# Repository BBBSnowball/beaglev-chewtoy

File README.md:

This is a fairly simple little board targetted at the BeagleV, but likely usable for anything that uses a 2x20 pin header.

The board takes the existing 2x20 header and either via a through-hole, or smt, header extends it away from the board
(assuming the connector is on the edge), and rotates it 180deg so if you happen to have a large heat sink, or something
else that's blocking the pins they might still be accessible for hats, etc. Most pre-production beta BeagleV boards have a
large heatsink out of an abundance of caution but this is not required and won't be used for production units.

This fork adds:
- LEDs: They are behind a buffer so the SoC or external device doesn't have to drive their current.
- series resistors: They provide some protection if you accidentally connect two outputs or while the SoC is driving
  the pins during reset. Remove them or use lower values if they impact high speed signals.
- JTAG headers: ARM 10-pin (2.54 mm and 1.27 mm, via ribbon cable), Sipeed RV Debugger (directly plugged into the board)
- a second header for debugging (e.g. attach a hat and a logic analyzer at the same time)
- UART connector
- pullups for I2C

All additional features are optional. Don't place the things that you don't need and you can close the solder jumper
below the series resistors if you don't want those. However, if you don't need any of them, I suggest that you use warthog9's
board: It's half the size and doesn't extend to the sides. Mine sacrifices that for a bit more functionality.

Jumpers:
- enable LEDs
- enable RX/TX on the Sipeed connector
  - You have to disable that if you want to use a different UART adapter, e.g. if you
    have trouble assigning different drivers to the parts of the FT2232H on Windows.
  - If you are on Linux, close the solder jumpers and omit the jumpers.
- connect 3.3V and/or 5V to Sipeed connector (solder jumpers)
  - The adapter doesn't need any reference voltage and it doesn't provide enough current to power the board so you should keep them open.
- swap TDI/TDO on the ARM connectors (solder jumpers)
  - I haven't tested the pinout yet so just in case...
- disconnect GND from pin 9 of the ARM connectors (GNDDetect)
- disconnect 3.3V from pin 1 of the ARM connectors
  - JTAG adapters with level shifters will use this to detect the target voltage.
  - If your adapter tries to power the target via this pin, cut the jumper to avoid that.

# Where to get one built

* OSH Park https://oshpark.com/shared_projects/uNRCdQbW (TODO: update this for the fork)

# License and Copyright
(C) John 'Warthog9' Hawley 2021, snowball 2021
CC-BY-SA 4.0

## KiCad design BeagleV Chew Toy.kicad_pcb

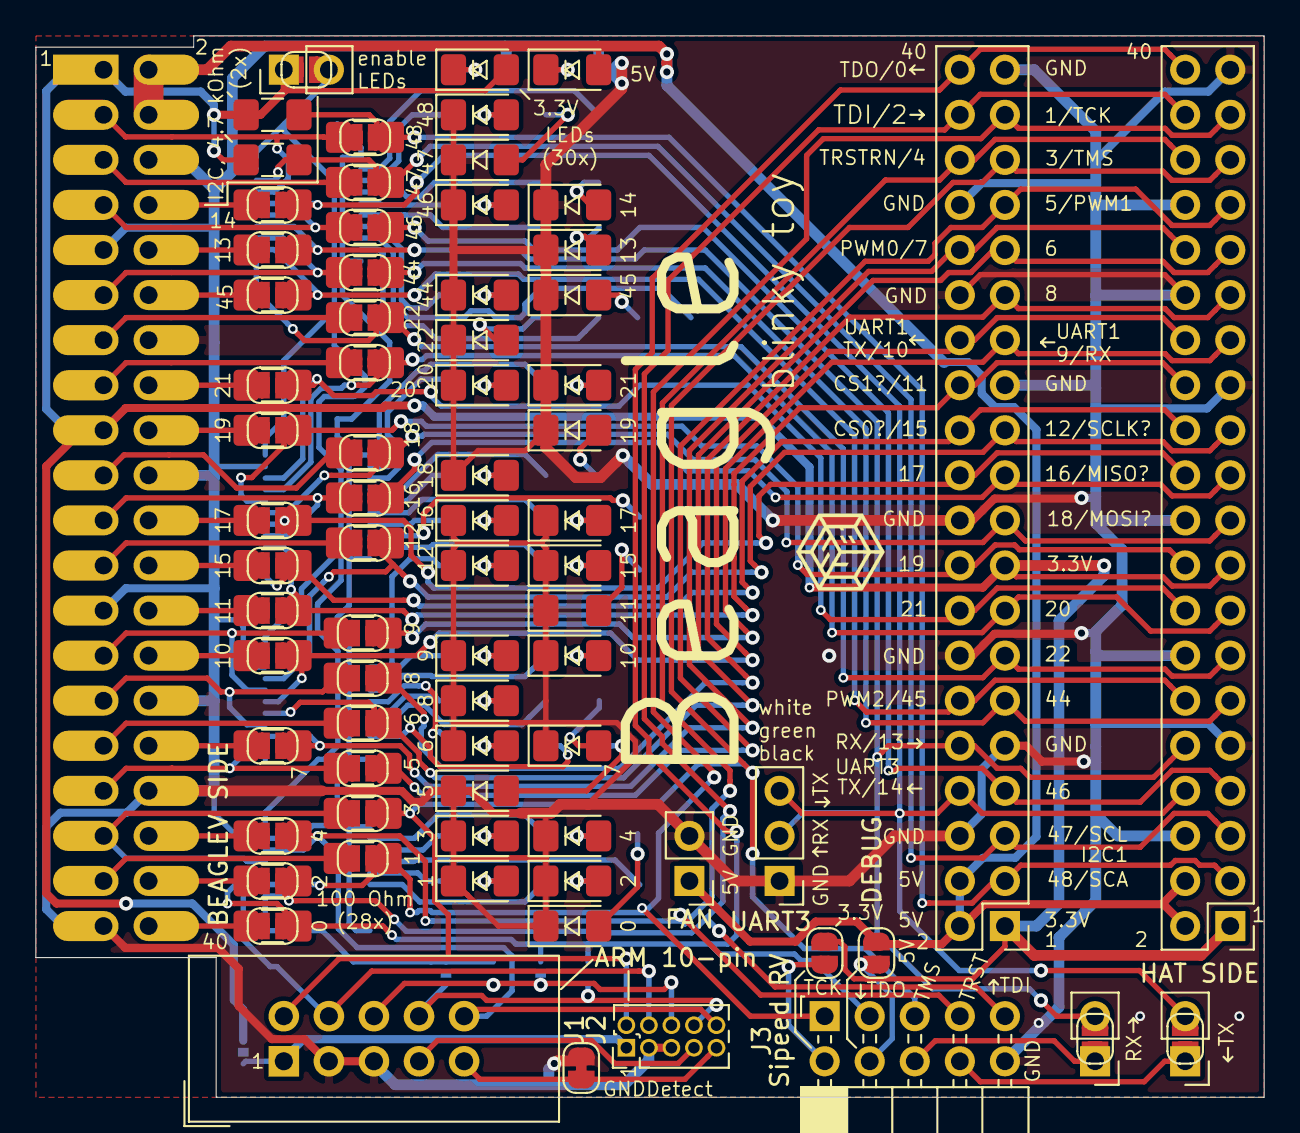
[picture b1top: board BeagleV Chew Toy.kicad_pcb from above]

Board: 2 copper layers, 69.2 x 59.8 mm, 148 parts (0 on the bottom side), 127 nets.

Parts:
BEAGLEVSIDE1: PINHD-2X20; PinSocket_2x20_P2.54mm_Vertical_THTSMD
C1, C2, C3, C4: 100nF; C_1206_3216Metric_Pad1.42x1.75mm_HandSolder
D1, D2, D3, D5, D7, D8, D10, D11, D12, D13, D15, D16, D18, D19, D21, D22, D23, D24, D26, D27, D28, D29, D31, D32, D33, D35, D36, D37, D38, D40: LED; LED_1206_3216Metric_Pad1.42x1.75mm_HandSolder
DEBUG1: PINHD-2X20-BIG; PinHeader_2x20_P2.54mm_Vertical
FAN1: PINHD-1X2; PinHeader_1x02_P2.54mm_Vertical
HATSIDE1: PINHD-2X20-BIG; PinHeader_2x20_P2.54mm_Vertical
J1: Conn_02x05_Counter_Clockwise; IDC-Header_2x05_P2.54mm_Vertical
J2: Conn_02x05_Counter_Clockwise; PinHeader_2x05_P1.27mm_Vertical
J3: Conn_02x05_Counter_Clockwise; PinSocket_2x05_P2.54mm_Horizontal
JP1, JP2, JP3, JP4, JP5, JP6, JP7, JP8, JP9, JP10, JP11, JP12, JP13, JP14, JP15, JP17, JP18, JP19, JP20, JP21, JP22, JP23, JP24, JP25, JP26, JP27, JP28, JP29, JP30, JP31, JP34, JP35, JP37, JP39, JP41: SolderJumper_2_Bridged; SolderJumper-2_P1.3mm_Open_RoundedPad1.0x1.5mm
JP16, JP32, JP33, JP42: SolderJumper_2_Bridged; SolderJumper-2_P1.3mm_Bridged_RoundedPad1.0x1.5mm
JP36, JP38, JP40: Jumper; PinHeader_1x02_P2.54mm_Vertical
R1, R2, R3, R4, R5, R6, R7, R8, R9, R10, R11, R12, R13, R14, R15, R16, R17, R18, R19, R20, R21, R22, R23, R24, R25, R26, R27, R28: 100R; R_1206_3216Metric_Pad1.42x1.75mm_HandSolder
R31, R32, R33, R35, R36, R37, R38, R39, R40, R41, R42, R43, R44, R45, R46, R47, R48, R49, R50, R51, R52, R53, R54, R55, R56, R57, R59, R60, R63, R64: 1k; R_1206_3216Metric_Pad1.42x1.75mm_HandSolder
R61, R62: 4k7; R_1206_3216Metric_Pad1.42x1.75mm_HandSolder
U1, U2, U3, U4: 74HC245; TSSOP-20_4.4x6.5mm_P0.65mm
UART1: PINHD-1X2; PinHeader_1x03_P2.54mm_Vertical

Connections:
+3V3: BEAGLEVSIDE1.1, BEAGLEVSIDE1.17, D1.2, DEBUG1.1, DEBUG1.17, HATSIDE1.1, HATSIDE1.17, JP30.2, JP40.1, JP41.1, JP42.1, R61.1, R62.1
+5V: BEAGLEVSIDE1.2, BEAGLEVSIDE1.4, D2.2, DEBUG1.2, DEBUG1.4, FAN1.1, HATSIDE1.2, HATSIDE1.4, JP31.2
/GPIO0_TDO_FROM_SOC: DEBUG1.40, HATSIDE1.40, J3.3, JP29.2, JP32.2, JP35.2, R28.1, U4.16
/GPIO1_TCK: DEBUG1.37, HATSIDE1.37, J1.4, J2.4, J3.1, JP15.1, R15.2, U4.15
/GPIO2_TDI_TO_SOC: DEBUG1.38, HATSIDE1.38, J3.9, JP28.2, JP33.2, JP34.2, R27.1, U4.11, U4.12, U4.13, U4.14
/GPIO3_TMS: DEBUG1.35, HATSIDE1.35, J1.2, J2.2, J3.5, JP14.1, R14.2
/GPIO4_TRSTN: DEBUG1.36, HATSIDE1.36, J1.10, J2.10, J3.7, JP27.2, R26.1, U4.18
/GPIO5/PWM: DEBUG1.33, HATSIDE1.33, JP13.1, R13.2
/GPIO6: DEBUG1.31, HATSIDE1.31, JP12.1, R12.2, U3.15
/GPIO7/PWM: DEBUG1.32, HATSIDE1.32, JP26.2, R25.1, U3.13
/GPIO8: DEBUG1.29, HATSIDE1.29, JP11.1, R11.2
/GPIO9: DEBUG1.27, HATSIDE1.27, JP10.1, R10.2
/GPIO10: DEBUG1.28, HATSIDE1.28, JP25.2, R24.1, U3.16
/GPIO11/CS1: DEBUG1.26, HATSIDE1.26, JP24.2, R23.1, U2.12
/GPIO12/SCLK: DEBUG1.23, HATSIDE1.23, JP9.1, R9.2, U3.18
/GPIO13/RX: DEBUG1.10, HATSIDE1.10, JP18.2, JP38.2, JP39.2, R17.1, U1.14, UART1.2
/GPIO14/TX: DEBUG1.8, HATSIDE1.8, JP17.2, JP36.2, JP37.2, R16.1, U1.16, UART1.3
/GPIO15/CS0: DEBUG1.24, HATSIDE1.24, JP23.2, R22.1, U2.11
/GPIO16/MISO: DEBUG1.21, HATSIDE1.21, JP8.1, R8.2
/GPIO17: DEBUG1.22, HATSIDE1.22, JP22.2, R21.1, U2.14
/GPIO18/MOSI: DEBUG1.19, HATSIDE1.19, JP7.1, R7.2, U2.15
/GPIO19: DEBUG1.18, HATSIDE1.18, JP21.2, R20.1, U2.16
/GPIO20: DEBUG1.15, HATSIDE1.15, JP6.1, R6.2, U2.17
/GPIO21: DEBUG1.16, HATSIDE1.16, JP20.2, R19.1, U2.18
/GPIO22: DEBUG1.13, HATSIDE1.13, JP5.1, R5.2, U1.11
/GPIO44: DEBUG1.11, HATSIDE1.11, JP4.1, R4.2
/GPIO45: DEBUG1.12, HATSIDE1.12, JP19.2, R18.1, U1.12
/GPIO46: DEBUG1.7, HATSIDE1.7, JP3.1, R3.2
/GPIO47/SCL: DEBUG1.5, HATSIDE1.5, JP2.1, R2.2, R62.2, U1.18
/GPIO48/SDA: DEBUG1.3, HATSIDE1.3, JP1.1, R1.2, R61.2
/P3: BEAGLEVSIDE1.3, JP1.2, R1.1, U1.17
/P7: BEAGLEVSIDE1.7, JP3.2, R3.1, U1.15
/P11: BEAGLEVSIDE1.11, JP4.2, R4.1, U1.13
/P21: BEAGLEVSIDE1.21, JP8.2, R8.1, U2.13
/P27: BEAGLEVSIDE1.27, JP10.2, R10.1, U3.17
/P29: BEAGLEVSIDE1.29, JP11.2, R11.1, U3.14
/P33: BEAGLEVSIDE1.33, JP13.2, R13.1, U3.11, U3.12
/P35: BEAGLEVSIDE1.35, JP14.2, R14.1, U4.17
GND: BEAGLEVSIDE1.6, BEAGLEVSIDE1.9, BEAGLEVSIDE1.14, BEAGLEVSIDE1.20, BEAGLEVSIDE1.25, BEAGLEVSIDE1.30, BEAGLEVSIDE1.34, BEAGLEVSIDE1.39, C1.2, C2.2, C3.2, C4.2, D3.1, D5.1, D7.1, D8.1, D10.1, D11.1, D12.1, D13.1, D15.1, D16.1, D18.1, D19.1, D21.1, D22.1, D23.1, D24.1, D26.1, D27.1, D28.1, D29.1, D31.1, D32.1, D33.1, D35.1, D36.1, D37.1, D38.1, D40.1, DEBUG1.6, DEBUG1.9, DEBUG1.14, DEBUG1.20, DEBUG1.25, DEBUG1.30, DEBUG1.34, DEBUG1.39, FAN1.2, HATSIDE1.6, HATSIDE1.9, HATSIDE1.14, HATSIDE1.20, HATSIDE1.25, HATSIDE1.30, HATSIDE1.34, HATSIDE1.39, J1.3, J1.5, J2.3, J2.5, J3.10, JP16.1, R63.2, R64.2, U1.1, U1.10, U1.19, U2.1, U2.10, U2.19, U3.1, U3.10, U3.19, U4.1, U4.10, U4.19, UART1.1
unnamed: BEAGLEVSIDE1.5, JP2.2, R2.1
unnamed: BEAGLEVSIDE1.8, JP17.1, R16.2
unnamed: BEAGLEVSIDE1.10, JP18.1, R17.2
unnamed: BEAGLEVSIDE1.12, JP19.1, R18.2
unnamed: BEAGLEVSIDE1.13, JP5.2, R5.1
unnamed: BEAGLEVSIDE1.15, JP6.2, R6.1
unnamed: BEAGLEVSIDE1.16, JP20.1, R19.2
unnamed: BEAGLEVSIDE1.18, JP21.1, R20.2
unnamed: BEAGLEVSIDE1.19, JP7.2, R7.1
unnamed: BEAGLEVSIDE1.22, JP22.1, R21.2
unnamed: BEAGLEVSIDE1.23, JP9.2, R9.1
unnamed: BEAGLEVSIDE1.24, JP23.1, R22.2
unnamed: BEAGLEVSIDE1.26, JP24.1, R23.2
unnamed: BEAGLEVSIDE1.28, JP25.1, R24.2
unnamed: BEAGLEVSIDE1.31, JP12.2, R12.1
unnamed: BEAGLEVSIDE1.32, JP26.1, R25.2
unnamed: BEAGLEVSIDE1.36, JP27.1, R26.2
unnamed: BEAGLEVSIDE1.37, JP15.2, R15.1
unnamed: BEAGLEVSIDE1.38, JP28.1, R27.2
unnamed: BEAGLEVSIDE1.40, JP29.1, R28.2
unnamed: D1.1, R63.1
unnamed: D2.1, R64.1
unnamed: D3.2, R31.2
unnamed: D5.2, R33.2
unnamed: D7.2, R35.2
unnamed: D8.2, R36.2
unnamed: D10.2, R38.2
unnamed: D11.2, R39.2
unnamed: D12.2, R40.2
unnamed: D13.2, R41.2
unnamed: D15.2, R43.2
unnamed: D16.2, R44.2
unnamed: D18.2, R46.2
unnamed: D19.2, R47.2
unnamed: D21.2, R49.2
unnamed: D22.2, R50.2
unnamed: D23.2, R51.2
unnamed: D24.2, R52.2
unnamed: D26.2, R54.2
unnamed: D27.2, R55.2
unnamed: D28.2, R56.2
unnamed: D29.2, R57.2
unnamed: D31.2, R59.2
unnamed: D32.2, R60.2
unnamed: D33.2, R37.2
unnamed: D35.2, R53.2
unnamed: D36.2, R42.2
unnamed: D37.2, R45.2
unnamed: D38.2, R48.2
unnamed: D40.2, R32.2
unnamed: J1.1, J2.1, JP42.2
unnamed: J1.6, J2.6, JP32.1, JP34.1
unnamed: J1.7, J2.7
unnamed: J1.8, J2.8, JP33.1, JP35.1
unnamed: J1.9, J2.9, JP16.2
unnamed: J3.2, JP30.1
unnamed: J3.4, JP31.1
unnamed: J3.6, JP38.1, JP39.1
unnamed: J3.8, JP36.1, JP37.1
unnamed: R31.1, U1.3
unnamed: R32.1, U4.4
unnamed: R33.1, U1.2
unnamed: R35.1, U1.5
unnamed: R36.1, U1.4
unnamed: R37.1, U3.8
unnamed: R38.1, U1.6
unnamed: R39.1, U1.7
unnamed: R40.1, U1.8
unnamed: R41.1, U1.9
unnamed: R42.1, U4.2
unnamed: R43.1, U2.3
unnamed: R44.1, U2.2
unnamed: R45.1, U4.5
unnamed: R46.1, U2.4
unnamed: R47.1, U2.5
unnamed: R48.1, U4.6
unnamed: R49.1, U2.7
unnamed: R50.1, U2.6
unnamed: R51.1, U3.2
unnamed: R52.1, U2.9
unnamed: R53.1, U4.3
unnamed: R54.1, U2.8
unnamed: R55.1, U3.3
unnamed: R56.1, U3.4
unnamed: R57.1, U3.6
unnamed: R59.1, U3.5
unnamed: R60.1, U3.7
VCC: C1.1, C2.1, C3.1, C4.1, JP40.2, JP41.2, U1.20, U2.20, U3.20, U4.20

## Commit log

2021-05-04 import into Kicad
2021-05-04 add PCB, slightly cleaned up
2021-05-04 replace connectors
    The footprints aren't the same anyway so let's use the Kicad parts.
2021-05-04 add most of the parts that we need
2021-05-05 place LEDs and resistors
2021-05-05 3/4 of LEDs routed
2021-05-05 LEDs done
2021-05-05 use elonged pads on Beagle-side header
2021-05-05 main part of the PCB is done
2021-05-05 small silk improvements
2021-05-06 mostly done
2021-05-06 rotate text in silk
    Some of it was in a different orientation than the others.
2021-05-06 bugfix: lower left corner would have collided with heatsink mount
2021-05-06 replace images, remove Eagle files
2021-05-06 add UART1 and PWM2 to silk screen
    also add the .sch file again...
2021-05-06 add interactive BOM
2021-05-09 add wire colors to UART connector
2021-05-09 fixup: swap RX/TX on Sipeed connector
2021-05-09 adjust README
2021-05-12 add questionmark to SPI pins in silk, generate gerbers
2021-05-12 OSHPark needs different naming for the gerber layers
2021-05-24 update schematic PDF and interactive BOM
2021-06-06 fix two small issues
    - PCB might collide with a heatsink mount to the right of the Beagle-V side
    connector. If so, the involved materials should be flexible enough to
    "resolve" this with a bit of force. Anyway, we can add a cutout to avoid
    that problem in the first place.
    - Silk is swapped for the 5V and 3.3V solder jumpers near the Sipeed connector.
    Gerbers are updated but IBOM is not because there are hardly any changes.
2021-06-11 PCBA files for JLC as exported by EasyEDA and fixed for bottom side - only valid for bottom side!
    Check component placement in the online preview before you order.

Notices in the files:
BeagleV Chew Toy.kicad_pcb:
(C) 2021 snowball
CC-BY-SA 4.0
